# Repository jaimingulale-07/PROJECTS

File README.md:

# 🎨 Jaimin’s Project Playground  

🎮 **Where Ideas Turn Into Reality**  
Hey there! I’m Jaimin Gulale (`jaimingulale-07`), and this is my *Project Playground*—a sandbox for my tech experiments. From FPGA wizardry to digital design and simulations, this repo’s got it all. Ready to explore? Let’s roll!

---

## 🎲 The Project Lineup  
Here’s what’s spinning in the playground right now:

### 1. RISC-V VLSI Emulator  
📄 **[Report: CA_22bec017_22bec044.pdf](https://github.com/jaimingulale-07/PROJECTS/blob/main/CA_22bec017_22bec044.pdf)**  
📦 **[Project Files: RISC-V.zip](https://github.com/jaimingulale-07/PROJECTS/blob/main/RISC-V.zip)**  
- **What It’s About**: A web-based RISC-V emulator designed to simulate the execution of RISC-V assembly instructions, showcasing ECE core concepts like instruction cycles, register updates, and memory management.  
- **Tech Stack**: ASP.NET Core (C#), SQLite, RISC-V ISA, VLSI concepts  
- **Status**:   

---

### 2. IP_FINAL Image Processing Project  
📄 **[Report: IP_FINAL (2).pdf](https://github.com/jaimingulale-07/PROJECTS/blob/main/IP_FINAL%20(2).pdf)**  
- **What It’s About**: Advanced image processing techniques implemented using MATLAB and Python, focusing on image enhancement, noise reduction, and feature extraction.  
- **Tech Stack**: MATLAB, Python (NumPy, OpenCV)  
- **Status**:   

---

### 3. Shift Testing Project  
📄 **[Shift Testing Report](https://github.com/jaimingulale-07/PROJECTS/blob/main/Shift_Testing_Report.pdf)**  
- **What It’s About**: Evaluating the performance and accuracy of shift operations (left shift, right shift, arithmetic and logical shifts) in hardware design and simulation.  
- **Tech Stack**: Verilog, MATLAB, Simulation Tools  
- **Status**:   

---

### 4. FPGA Image Compression  
📄 **[Report: fpga_report_22bec044.pdf](https://github.com/jaimingulale-07/PROJECTS/blob/main/fpga_report_22bec044.pdf)**  
- **What It’s About**: Squeezing images down to size using FPGA hardware—fast, efficient, awesome.  
- **Tech Stack**: FPGA (Verilog/VHDL), Quartus (if applicable)  
- **Status**:   

---

### 5. MnM Simulation Demo  
🎥 **[Video: MnM simulation video (1).mp4](https://github.com/jaimingulale-07/PROJECTS/blob/main/MnM%20simulation%20video%20(1).mp4)**  
- **What It’s About**: A visual demo of a simulation—think moving parts, cool visuals, and tech in action.  
- **Tech Stack**: MATLAB, Python (if applicable)  
- **Status**:   

---

### 6. Digital Logic Design Assignment  
📄 **[Report: SA -DLD.pdf](https://github.com/jaimingulale-07/PROJECTS/blob/main/SA%20-DLD.pdf)**  
- **What It’s About**: A deep dive into Digital Logic Design—gates, circuits, and all that binary goodness.  
- **Tech Stack**: Logisim, Verilog (if applicable)  
- **Status**:   

---

### 7. MnM Special Assignment  
📄 **[Report: mnm special assignment.pdf](https://github.com/jaimingulale-07/PROJECTS/blob/main/mnm%20special%20assignment.pdf)**  
- **What It’s About**: The brains behind the MnM simulation—details, theory, and results.  
- **Tech Stack**: Python, MATLAB (if applicable)  
- **Status**:   

---

### 8. Voltage Sense Amplifier (LTspice Design)  
📄 **[Schematic: voltage_sense_amplifier.asc](https://github.com/jaimingulale-07/PROJECTS/blob/main/voltage_sense_amplifier.asc)**  
🖼️ **[Circuit Image](https://github.com/jaimingulale-07/PROJECTS/blob/main/263d52f2-d812-44db-b12f-f698d1a84475.png)**  
- **What It’s About**: A sense amplifier built using PMOS and NMOS transistors in LTspice, designed for detecting small differential voltage changes in memory circuits or analog comparators.  
- **Tech Stack**: LTspice (Analog Simulation)  
- **Status**:   

#### 🖥️ Circuit Preview  

#### 🛠️ Simulation Setup  
- DC Sweep: `.dc V1 0 5 0.5`  
- Inputs: `V2 = 1.8V`, `V3 = 1.8V`  
- Output: Cross-coupled NMOS/PMOS structure behavior

*Open the `.asc` file in LTspice, press `F9`, and analyze how the amplifier reacts to differential inputs!*

---

## 🛠️ My Playground Gear  

---

## 🎯 How to Dive In  
1. **Clone It**: `git clone https://github.com/jaimingulale-07/PROJECTS.git`  
2. **Pick a Project**: Grab the PDFs, ZIP, or MP4 from the links above.  
3. **Get Involved**: Have feedback or ideas? Drop them in [Issues](https://github.com/jaimingulale-07/PROJECTS/issues)!  

---

## 🌐 Let’s Chat  
  
📧 Email: jaiminkumargulale@gmail.com  
*Hit me up if you’re into FPGA, simulations, or just geeky stuff!*  

---

## ✨ Why This Playground?  
Every project here is a puzzle I’ve pieced together—some with code, some with hardware, all with curiosity. What’s your next big play?  

---

**“Build it, test it, share it—that’s the game.”**

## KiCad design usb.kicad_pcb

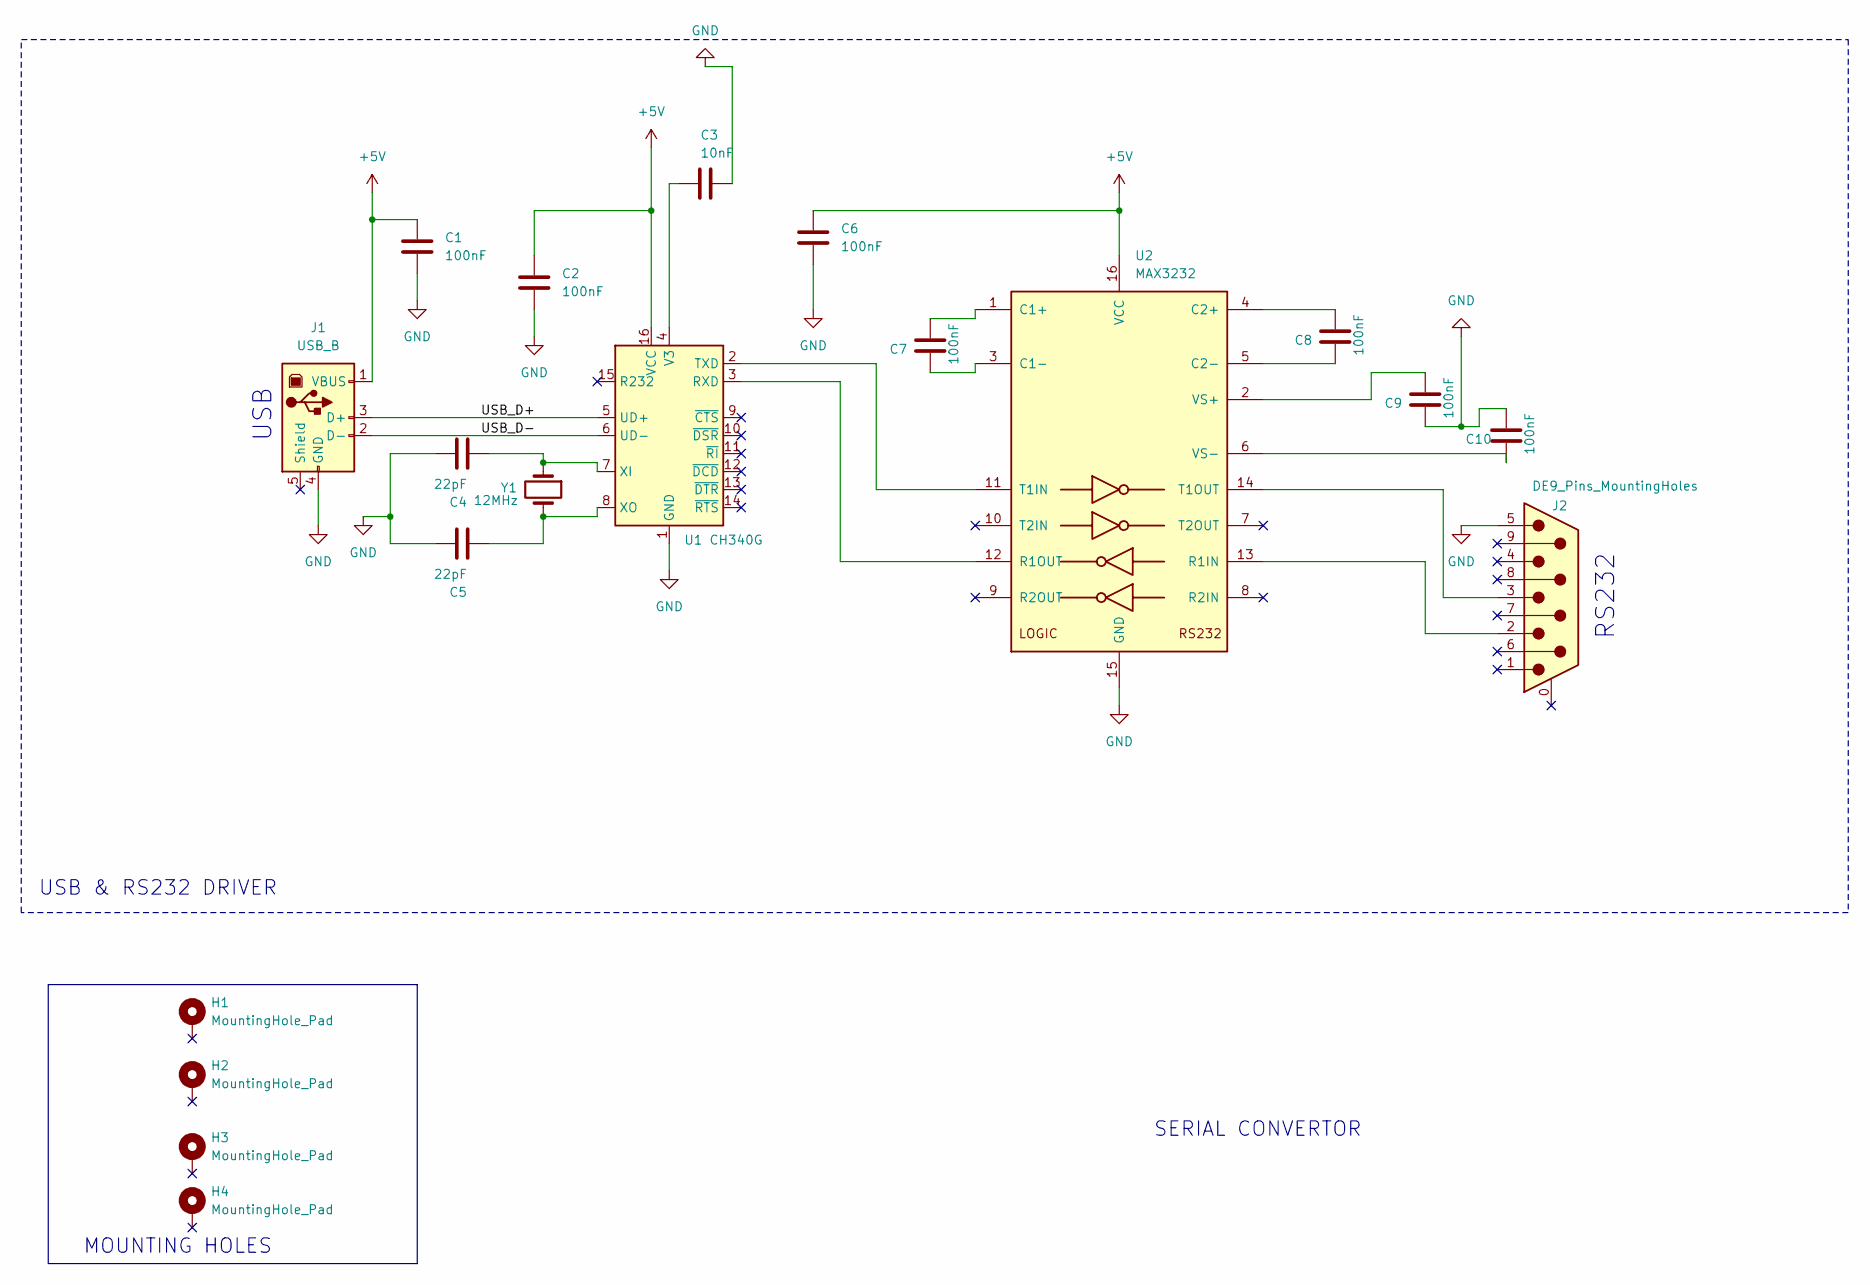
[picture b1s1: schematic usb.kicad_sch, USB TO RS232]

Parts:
C1, C2, C6, C7, C8, C9, C10: 100nF; C_0805_2012Metric
C3: 10nF; C_0805_2012Metric
C4, C5: 22pF; C_0805_2012Metric
H1, H2, H3, H4: MountingHole_Pad; MountingHole_3.2mm_M3_Pad_Via
J1: USB_B; USB_B_Lumberg_2411_02_Horizontal
J2: DE9_Pins_MountingHoles; DSUB-9_Socket_Horizontal_P2.77x2.84mm_EdgePinOffset4.94mm_H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
U1: CH340G; SOIC-16_3.9x9.9mm_P1.27mm
U2: MAX3232; SOIC-16_3.9x9.9mm_P1.27mm
Y1: 12MHz; Crystal_SMD_HC49-SD

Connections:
+5V: C1.1, C2.1, C6.1, J1.1 (VBUS), U1.16 (VCC), U2.16 (VCC)
/USB_D+: J1.3 (D+), U1.5 (UD+)
/USB_D-: J1.2 (D-), U1.6 (UD-)
GND: C1.2, C2.2, C3.1, C4.1, C5.1, C6.2, C9.1, C10.2, J1.4 (GND), J2.5, U1.1 (GND), U2.15 (GND)
unnamed: U1.3 (RXD), U2.12 (R1OUT)
unnamed: U1.2 (TXD), U2.11 (T1IN)
unnamed: C3.2, U1.4 (V3)
unnamed: C4.2, U1.7 (XI), Y1.1
unnamed: C5.2, U1.8 (XO), Y1.2
unnamed: C7.2, U2.1 (C1+)
unnamed: C7.1, U2.3 (C1-)
unnamed: C8.2, U2.4 (C2+)
unnamed: C8.1, U2.5 (C2-)
unnamed: J2.2, U2.13 (R1IN)
unnamed: J2.3, U2.14 (T1OUT)
unnamed: C9.2, U2.2 (VS+)
unnamed: C10.1, U2.6 (VS-)

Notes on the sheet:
USB & RS232 DRIVER
RS232
USB
MOUNTING HOLES
SERIAL CONVERTOR

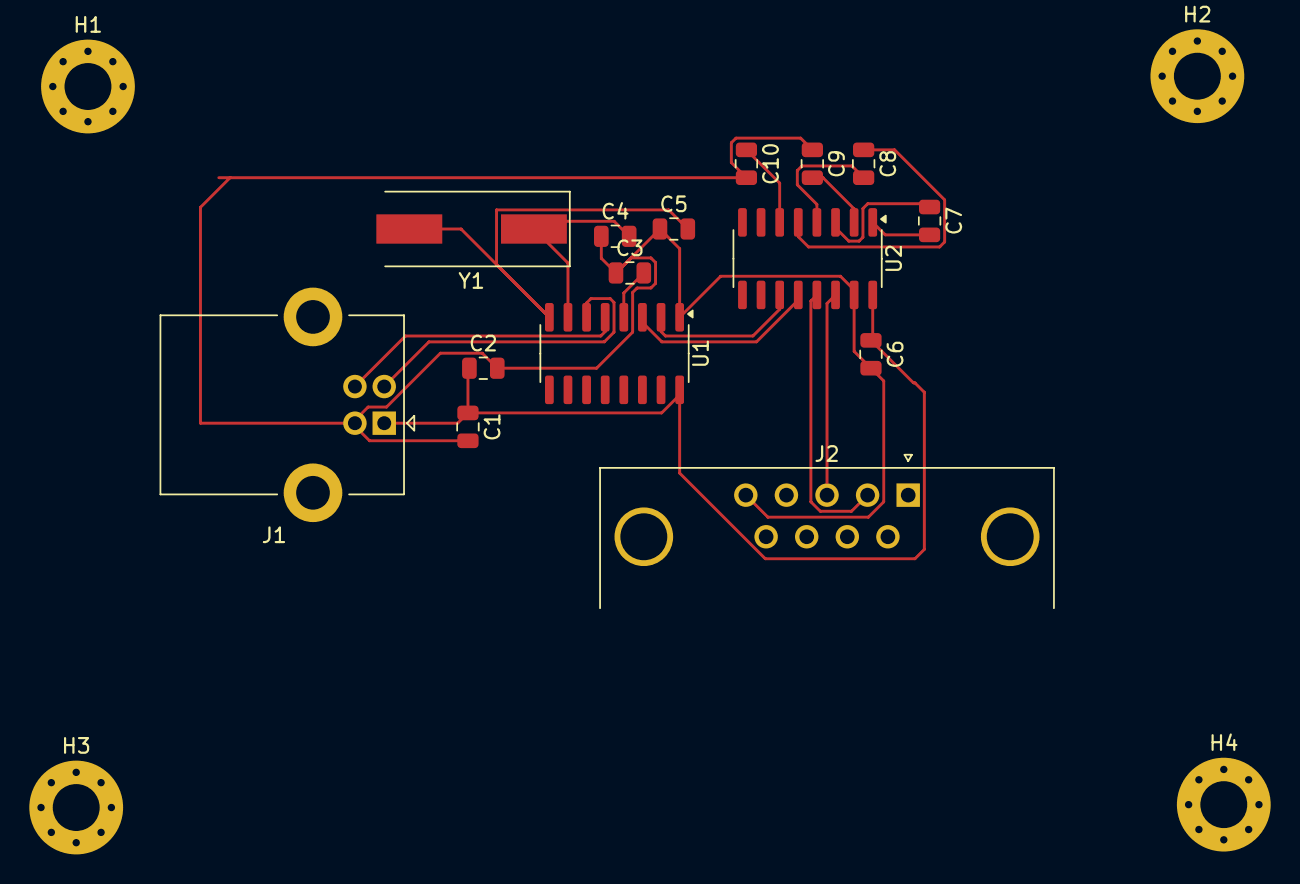
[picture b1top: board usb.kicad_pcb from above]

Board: 2 copper layers, 19 parts (0 on the bottom side), 17 nets.

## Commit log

2025-03-25 Added RISC-V.zip using Git LFS
2025-03-25 Added Drone Image Coordinate Finder project report
2025-03-25 Shift-Left Testing:
2025-03-25 RISC-V based emulator
2025-07-18 Rename pse.pdf to Shift_Testing_Report.pdf
